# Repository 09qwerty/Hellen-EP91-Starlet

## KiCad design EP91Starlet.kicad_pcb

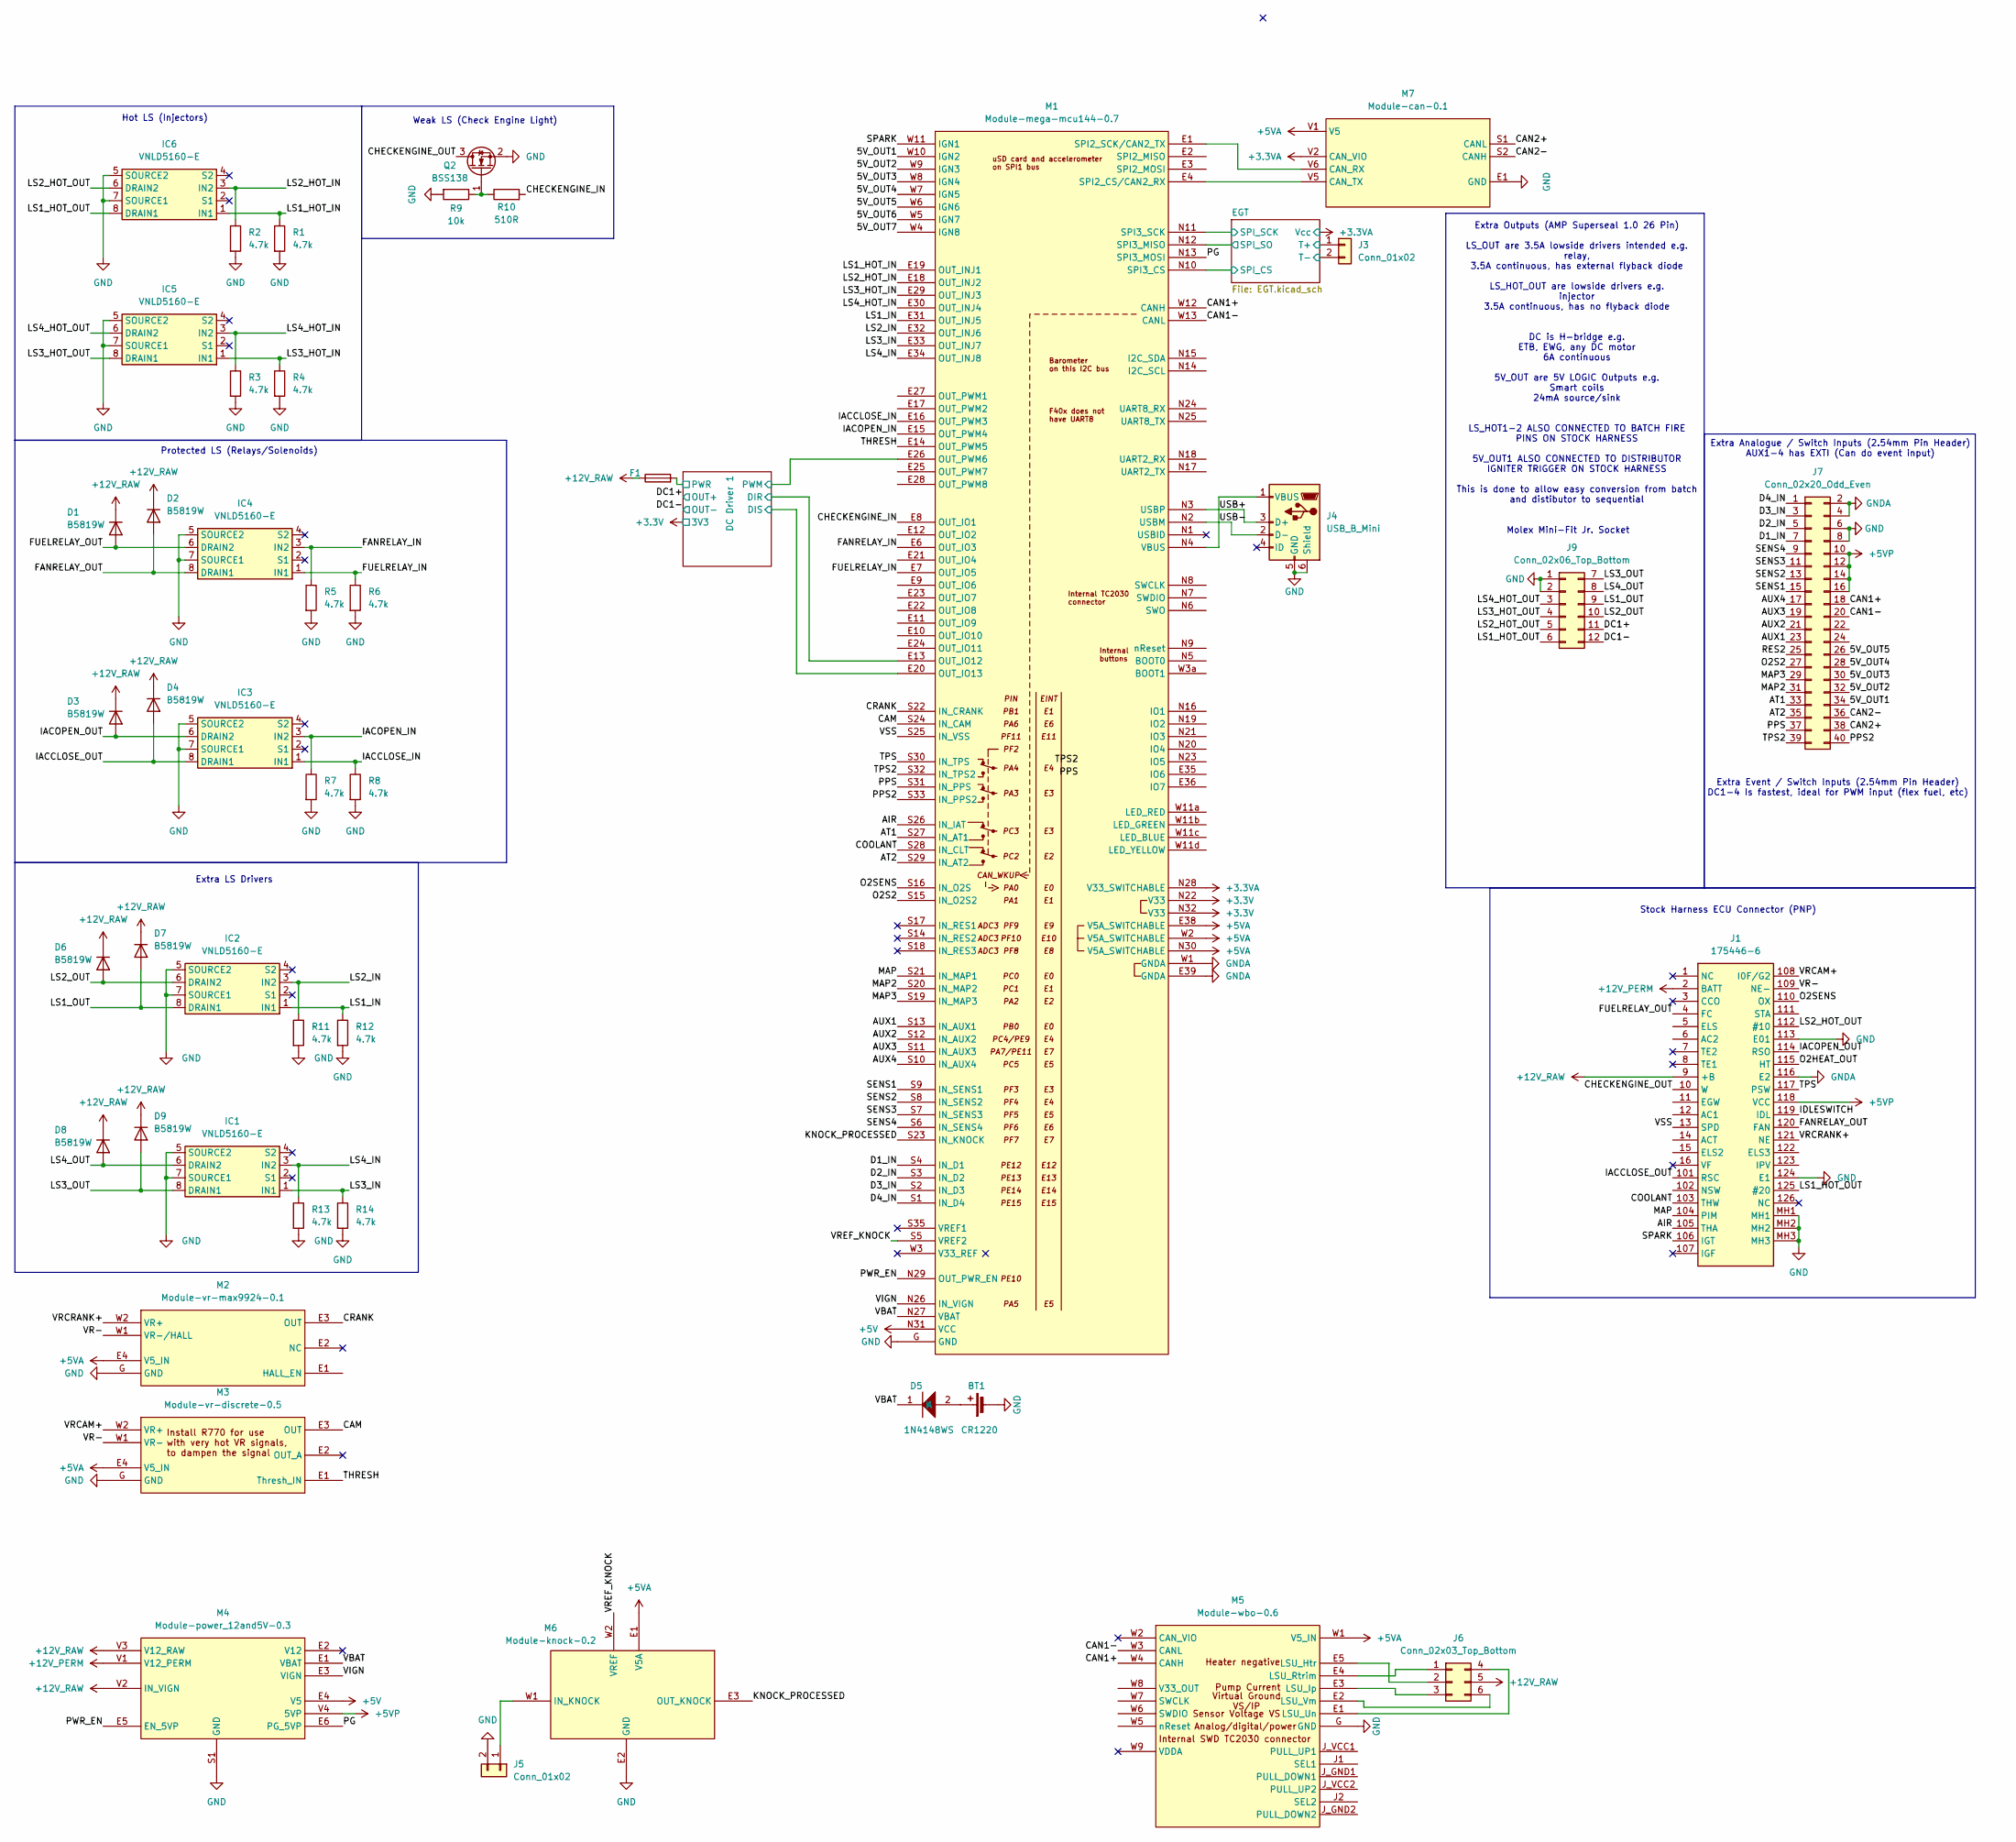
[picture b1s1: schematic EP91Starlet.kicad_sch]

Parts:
BT1: CR1220; CR1220-2; LCSC C70381
D1, D2, D3, D4, D6, D7, D8, D9: B5819W; D_SOD-123
D5: 1N4148WS; D_SOD-323; LCSC C2128
F1: Fuse; Fuse_1206_3216Metric_Pad1.42x1.75mm_HandSolder; LCSC C182446
IC1, IC2, IC3, IC4, IC5, IC6: VNLD5160-E; SOIC127P600X175-8N; Mouser Part Number 511-VNLD5160TR-E
J1: 175446-6; 1754466; Mouser Part Number 571-175446-6
J3, J5: Conn_01x02; PinHeader_1x02_P2.54mm_Vertical
J4: USB_B_Mini; USB_Mini-B_Wuerth_65100516121_Horizontal
J6: Conn_02x03_Top_Bottom; Molex_Mini-Fit_Jr_5566-06A_2x03_P4.20mm_Vertical
J7: Conn_02x20_Odd_Even; IDC-Header_2x20_P2.54mm_Vertical
J9: Conn_02x06_Top_Bottom; Molex_Mini-Fit_Jr_5566-12A_2x06_P4.20mm_Vertical
M1: Module-mega-mcu144-0.7; mega-mcu144
M2: Module-vr-max9924-0.1; vr-max9924
M3: Module-vr-discrete-0.5; vr-discrete
M4: Module-power_12and5V-0.3; power_12and5V
M5: Module-wbo-0.6; wbo
M6: Module-knock-0.2; knock
M7: Module-can-0.1; can
Q2: BSS138; SOT-23
R1, R2, R3, R4, R5, R6, R7, R8, R11, R12, R13, R14: 4.7k; R_0402_1005Metric
R9: 10k; R_0402_1005Metric
R10: 510R; R_0402_1005Metric

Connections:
+3.3V: M1.N22 (V33), M1.N32 (V33); also elsewhere on the board
+3.3VA: M1.N28 (V33_SWITCHABLE), M7.V2 (CAN_VIO); also elsewhere on the board
+5V: M1.N31 (VCC), M4.E4 (V5)
+5VA: M1.E38 (V5A_SWITCHABLE), M1.N30 (V5A_SWITCHABLE), M1.W2 (V5A_SWITCHABLE), M2.E4 (V5_IN), M3.E4 (V5_IN), M5.W1 (V5_IN), M6.E1 (V5A), M7.V1 (V5)
+5VP: J1.118 (VCC), J7.10, J7.12, J7.14, J7.16, M4.V4 (5VP)
+12V_PERM: J1.2 (BATT), M4.V1 (V12_PERM)
+12V_RAW: D1.1 (K), D2.1 (K), D3.1 (K), D4.1 (K), D6.1 (K), D7.1 (K), D8.1 (K), D9.1 (K), F1.1, J1.9 (+B), J6.5, M4.V2 (IN_VIGN), M4.V3 (V12_RAW)
/5V_OUT1: J7.34, M1.W10 (IGN2)
/5V_OUT2: J7.32, M1.W9 (IGN3)
/5V_OUT3: J7.30, M1.W8 (IGN4)
/5V_OUT4: J7.28, M1.W7 (IGN5)
/5V_OUT5: J7.26, M1.W6 (IGN6)
/5V_OUT6: M1.W5 (IGN7)
/5V_OUT7: M1.W4 (IGN8)
/AIR: J1.105 (THA), M1.S26 (IN_IAT)
/AT1: J7.33, M1.S27 (IN_AT1)
/AT2: J7.35, M1.S29 (IN_AT2)
/AUX1: J7.23, M1.S13 (IN_AUX1)
/AUX2: J7.21, M1.S12 (IN_AUX2)
/AUX3: J7.19, M1.S11 (IN_AUX3)
/AUX4: J7.17, M1.S10 (IN_AUX4)
/CAM: M1.S24 (IN_CAM), M3.E3 (OUT)
/CAN1+: J7.18, M1.W12 (CANH), M5.W4 (CANH)
/CAN1-: J7.20, M1.W13 (CANL), M5.W3 (CANL)
/CAN2+: J7.38, M7.S1 (CANL)
/CAN2-: J7.36, M7.S2 (CANH)
/CHECKENGINE_IN: M1.E8 (OUT_IO1), R10.2
/CHECKENGINE_OUT: J1.10 (W), Q2.3 (D)
/COOLANT: J1.103 (THW), M1.S28 (IN_CLT)
/CRANK: M1.S22 (IN_CRANK), M2.E3 (OUT)
/D1_IN: J7.7, M1.S4 (IN_D1)
/D2_IN: J7.5, M1.S3 (IN_D2)
/D3_IN: J7.3, M1.S2 (IN_D3)
/D4_IN: J7.1, M1.S1 (IN_D4)
/DC1+: J9.11; also elsewhere on the board
/DC1-: J9.12; also elsewhere on the board
/DC Driver 1/DIR: M1.E13 (OUT_IO12); also elsewhere on the board
/DC Driver 1/DIS: M1.E20 (OUT_IO13); also elsewhere on the board
/DC Driver 1/PWM: M1.E26 (OUT_PWM6); also elsewhere on the board
/DC Driver 1/PWR: F1.2; also elsewhere on the board
/EGT/SPI_CS: M1.N10 (SPI3_CS); also elsewhere on the board
/EGT/SPI_SCK: M1.N11 (SPI3_SCK); also elsewhere on the board
/EGT/SPI_SO: M1.N12 (SPI3_MISO); also elsewhere on the board
/EGT/T+: J3.1; also elsewhere on the board
/EGT/T-: J3.2; also elsewhere on the board
/FANRELAY_IN: IC4.3 (IN2), M1.E6 (OUT_IO3), R5.1
/FANRELAY_OUT: D2.2 (A), IC4.8 (DRAIN1), J1.120 (FAN)
/FUELRELAY_IN: IC4.1 (IN1), M1.E7 (OUT_IO5), R6.1
/FUELRELAY_OUT: D1.2 (A), IC4.6 (DRAIN2), J1.4 (FC)
/IACCLOSE_IN: IC3.1 (IN1), M1.E16 (OUT_PWM3), R8.1
/IACCLOSE_OUT: D4.2 (A), IC3.8 (DRAIN1), J1.101 (RSC)
/IACOPEN_IN: IC3.3 (IN2), M1.E15 (OUT_PWM4), R7.1
/IACOPEN_OUT: D3.2 (A), IC3.6 (DRAIN2), J1.114 (RSO)
/IDLESWITCH: J1.119 (IDL)
/KNOCK_PROCESSED: M1.S23 (IN_KNOCK), M6.E3 (OUT_KNOCK)
/LS1_HOT_IN: IC6.1 (IN1), M1.E19 (OUT_INJ1), R1.1
/LS1_HOT_OUT: IC6.8 (DRAIN1), J1.125 (#20), J9.6
/LS1_IN: IC2.1 (IN1), M1.E31 (OUT_INJ5), R12.1
/LS1_OUT: D7.2 (A), IC2.8 (DRAIN1), J9.9
/LS2_HOT_IN: IC6.3 (IN2), M1.E18 (OUT_INJ2), R2.1
/LS2_HOT_OUT: IC6.6 (DRAIN2), J1.112 (#10), J9.5
/LS2_IN: IC2.3 (IN2), M1.E32 (OUT_INJ6), R11.1
/LS2_OUT: D6.2 (A), IC2.6 (DRAIN2), J9.10
/LS3_HOT_IN: IC5.1 (IN1), M1.E29 (OUT_INJ3), R4.1
/LS3_HOT_OUT: IC5.8 (DRAIN1), J9.4
/LS3_IN: IC1.1 (IN1), M1.E33 (OUT_INJ7), R14.1
/LS3_OUT: D9.2 (A), IC1.8 (DRAIN1), J9.7
/LS4_HOT_IN: IC5.3 (IN2), M1.E30 (OUT_INJ4), R3.1
/LS4_HOT_OUT: IC5.6 (DRAIN2), J9.3
/LS4_IN: IC1.3 (IN2), M1.E34 (OUT_INJ8), R13.1
/LS4_OUT: D8.2 (A), IC1.6 (DRAIN2), J9.8
/MAP: J1.104 (PIM), M1.S21 (IN_MAP1)
/MAP2: J7.31, M1.S20 (IN_MAP2)
/MAP3: J7.29, M1.S19 (IN_MAP3)
/O2HEAT_OUT: J1.115 (HT)
/O2S2: J7.27, M1.S15 (IN_O2S2)
/O2SENS: J1.110 (OX), M1.S16 (IN_O2S)
/PG: M1.N13 (SPI3_MOSI), M4.E6 (PG_5VP)
/PPS: J7.37, M1.S31 (IN_PPS)
/PPS2: J7.40, M1.S33 (IN_PPS2)
/PWR_EN: M1.N29 (OUT_PWR_EN), M4.E5 (EN_5VP)
/RES2: J7.25
/SENS1: J7.15, M1.S9 (IN_SENS1)
/SENS2: J7.13, M1.S8 (IN_SENS2)
/SENS3: J7.11, M1.S7 (IN_SENS3)
/SENS4: J7.9, M1.S6 (IN_SENS4)
/SPARK: J1.106 (IGT), M1.W11 (IGN1)
/THRESH: M1.E14 (OUT_PWM5), M3.E1 (Thresh_IN)
/TPS: J1.117 (PSW), M1.S30 (IN_TPS)
/TPS2: J7.39, M1.S32 (IN_TPS2)
/VBAT: D5.1 (K), M1.N27 (VBAT), M4.E1 (VBAT)
/VIGN: M1.N26 (IN_VIGN), M4.E3 (VIGN)
/VR-: J1.109 (NE-), M2.W1 (VR-/HALL), M3.W1 (VR-)
/VRCAM+: J1.108 (I0F/G2), M3.W2 (VR+)
/VRCRANK+: J1.121 (NE), M2.W2 (VR+)
/VREF_KNOCK: M1.S5 (VREF2), M6.W2 (VREF)
/VSS: J1.13 (SPD), M1.S25 (IN_VSS)
GND: BT1.2 (-), IC1.5 (SOURCE2), IC1.7 (SOURCE1), IC2.5 (SOURCE2), IC2.7 (SOURCE1), IC3.5 (SOURCE2), IC3.7 (SOURCE1), IC4.5 (SOURCE2), IC4.7 (SOURCE1), IC5.5 (SOURCE2), IC5.7 (SOURCE1), IC6.5 (SOURCE2), IC6.7 (SOURCE1), J1.113 (E01), J1.124 (E1), J1.MH1, J1.MH2, J1.MH3, J4.5 (GND), J4.6 (Shield), J5.2, J7.6, J7.8, J9.1, J9.2, M1.G (GND), M2.G (GND), M3.G (GND), M4.S1 (GND), M5.G (GND), M6.E2 (GND), M7.E1 (GND), Q2.2 (S), R1.2, R2.2, R3.2, R4.2, R5.2, R6.2, R7.2, R8.2, R9.2, R11.2, R12.2, R13.2, R14.2; also elsewhere on the board
GNDA: J1.116 (E2), J7.2, J7.4, M1.E39 (GNDA), M1.W1 (GNDA)
unnamed: BT1.1 (+), D5.2 (A)
unnamed: J5.1, M6.W1 (IN_KNOCK)
unnamed: J6.1, M5.E4 (LSU_Rtrim)
unnamed: J6.2, M5.E5 (LSU_Htr)
unnamed: J6.3, M5.E3 (LSU_Ip)
unnamed: J6.4, M5.E1 (LSU_Un)
unnamed: J6.6, M5.E2 (LSU_Vm)
unnamed: M1.E4 (SPI2_CS/CAN2_RX), M7.V5 (CAN_TX)
unnamed: M1.E1 (SPI2_SCK/CAN2_TX), M7.V6 (CAN_RX)
unnamed: Q2.1 (G), R9.1, R10.1

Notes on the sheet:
Stock Harness ECU Connector (PNP)
Extra Outputs (AMP Superseal 1.0 26 Pin) LS_OUT are 3.5A lowside drivers intended e.g. relay, 3.5A continuous, has external flyback diode LS_HOT_OUT are lowside drivers e.g. injector 3.5A continuous, has no flyback diode DC is H-bridge e.g. ETB, EWG, any DC motor 6A continuous 5V_OUT are 5V LOGIC O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
Extra Event / Switch Inputs (2.54mm Pin Header) DC1-4 Is fastest, ideal for PWM input (flex fuel, etc)
Hot LS (Injectors)
Extra LS Drivers
Molex Mini-Fit Jr. Socket
Weak LS (Check Engine Light)
Extra Analogue / Switch Inputs (2.54mm Pin Header) AUX1-4 has EXTI (Can do event input)
Protected LS (Relays/Solenoids)

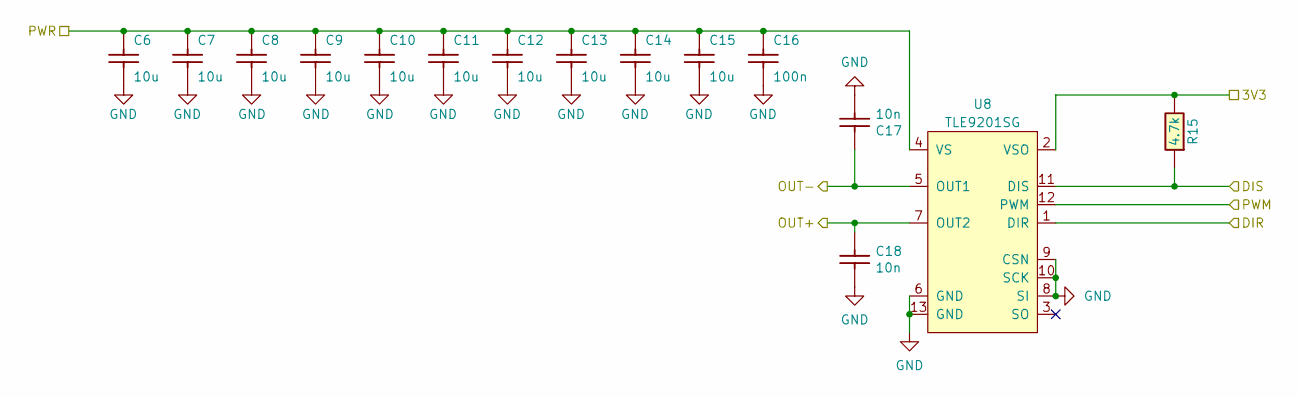
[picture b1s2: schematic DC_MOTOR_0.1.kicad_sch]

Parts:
C6, C7, C8, C9, C10, C11, C12, C13, C14, C15: 10u; C_0603_1608Metric; LCSC C15850
C16: 100n; C_0603_1608Metric; LCSC C14663
C17, C18: 10n; C_0603_1608Metric; LCSC C57112
R15: 4.7k; R_0603_1608Metric; LCSC C23162
U8: TLE9201SG; Infineon_PG-DSO-12-11; LCSC C112633

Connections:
+3.3V: R15.2, U8.2 (VSO); also elsewhere on the board
/DC1+: C18.2, U8.7 (OUT2); also elsewhere on the board
/DC1-: C17.2, U8.5 (OUT1); also elsewhere on the board
/DC Driver 1/DIR: U8.1 (DIR); also elsewhere on the board
/DC Driver 1/DIS: R15.1, U8.11 (DIS); also elsewhere on the board
/DC Driver 1/PWM: U8.12 (PWM); also elsewhere on the board
/DC Driver 1/PWR: C6.2, C7.2, C8.2, C9.2, C10.2, C11.2, C12.2, C13.2, C14.2, C15.2, C16.2, U8.4 (VS); also elsewhere on the board
GND: C6.1, C7.1, C8.1, C9.1, C10.1, C11.1, C12.1, C13.1, C14.1, C15.1, C16.1, C17.1, C18.1, U8.6 (GND), U8.8 (SI), U8.9 (CSN), U8.10 (SCK), U8.13 (GND); also elsewhere on the board

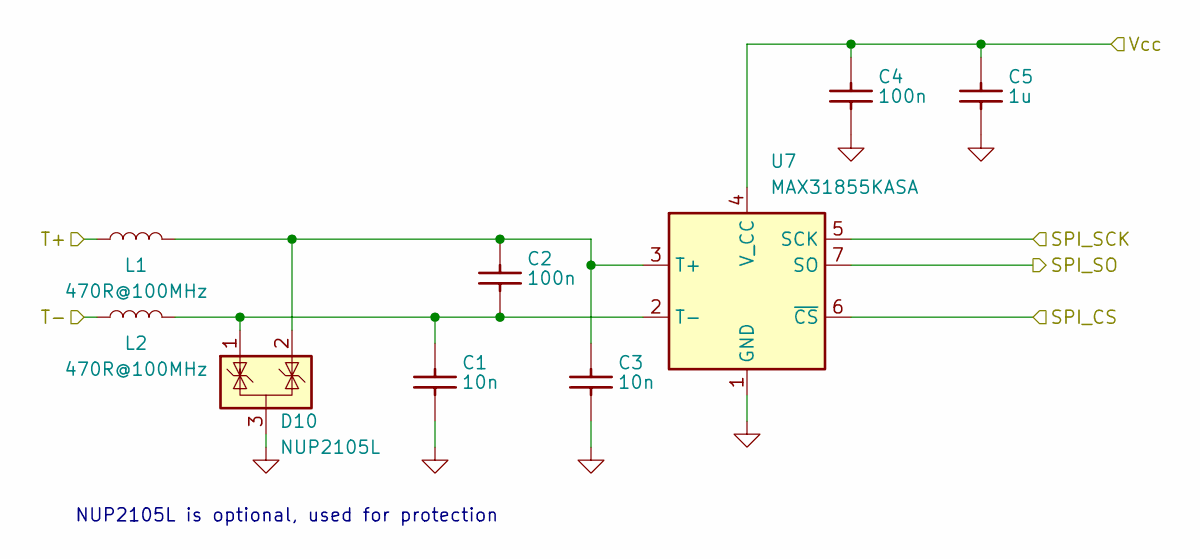
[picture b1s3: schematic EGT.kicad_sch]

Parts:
C1, C3: 10n; C_0603_1608Metric; LCSC C57112
C2, C4: 100n; C_0603_1608Metric; LCSC C14663
C5: 1u; C_0603_1608Metric; LCSC C15849
D10: NUP2105L; SOT-23; LCSC C284104
L1, L2: 470R@100MHz; L_0603_1608Metric; LCSC C97853
U7: MAX31855KASA; SOIC-8_3.9x4.9mm_P1.27mm; LCSC C52028

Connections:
+3.3VA: C4.2, C5.2, U7.4 (V_CC); also elsewhere on the board
/EGT/SPI_CS: U7.6 (~CS); also elsewhere on the board
/EGT/SPI_SCK: U7.5 (SCK); also elsewhere on the board
/EGT/SPI_SO: U7.7 (SO); also elsewhere on the board
/EGT/T+: L1.1; also elsewhere on the board
/EGT/T-: L2.1; also elsewhere on the board
GND: C1.1, C3.1, C4.1, C5.1, D10.3 (A), U7.1 (GND); also elsewhere on the board
unnamed: C2.2, C3.2, D10.2 (K), L1.2, U7.3 (T+)
unnamed: C1.2, C2.1, D10.1 (K), L2.2, U7.2 (T-)

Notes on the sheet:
NUP2105L is optional, used for protection

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
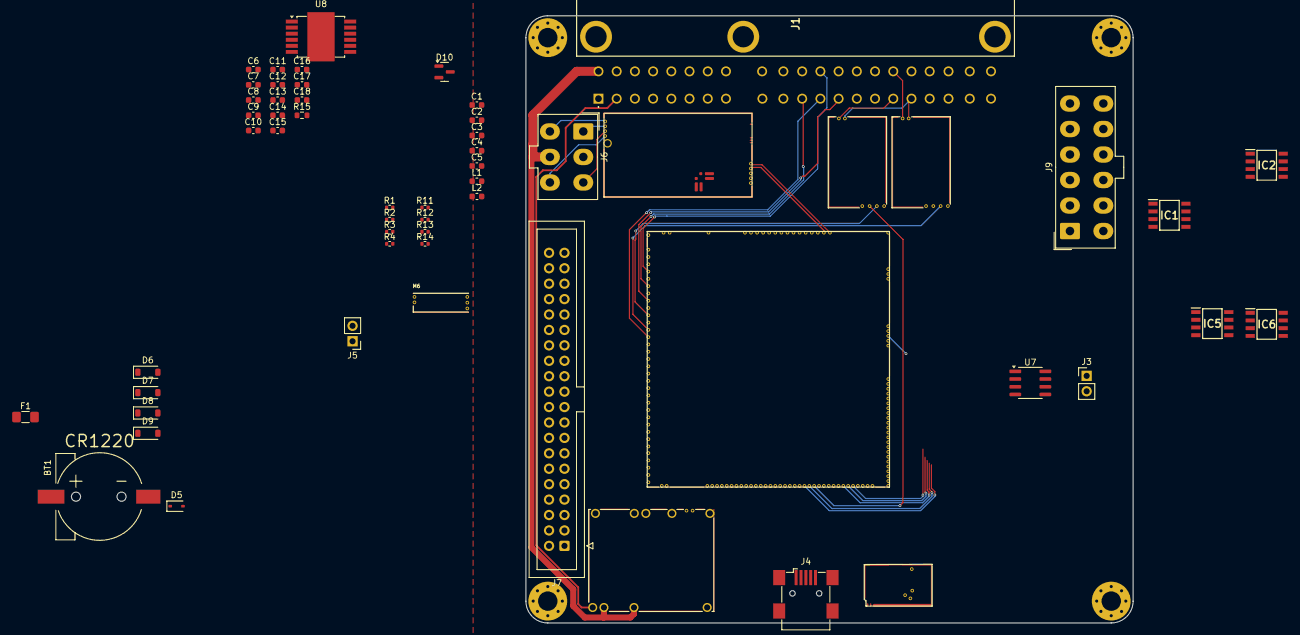
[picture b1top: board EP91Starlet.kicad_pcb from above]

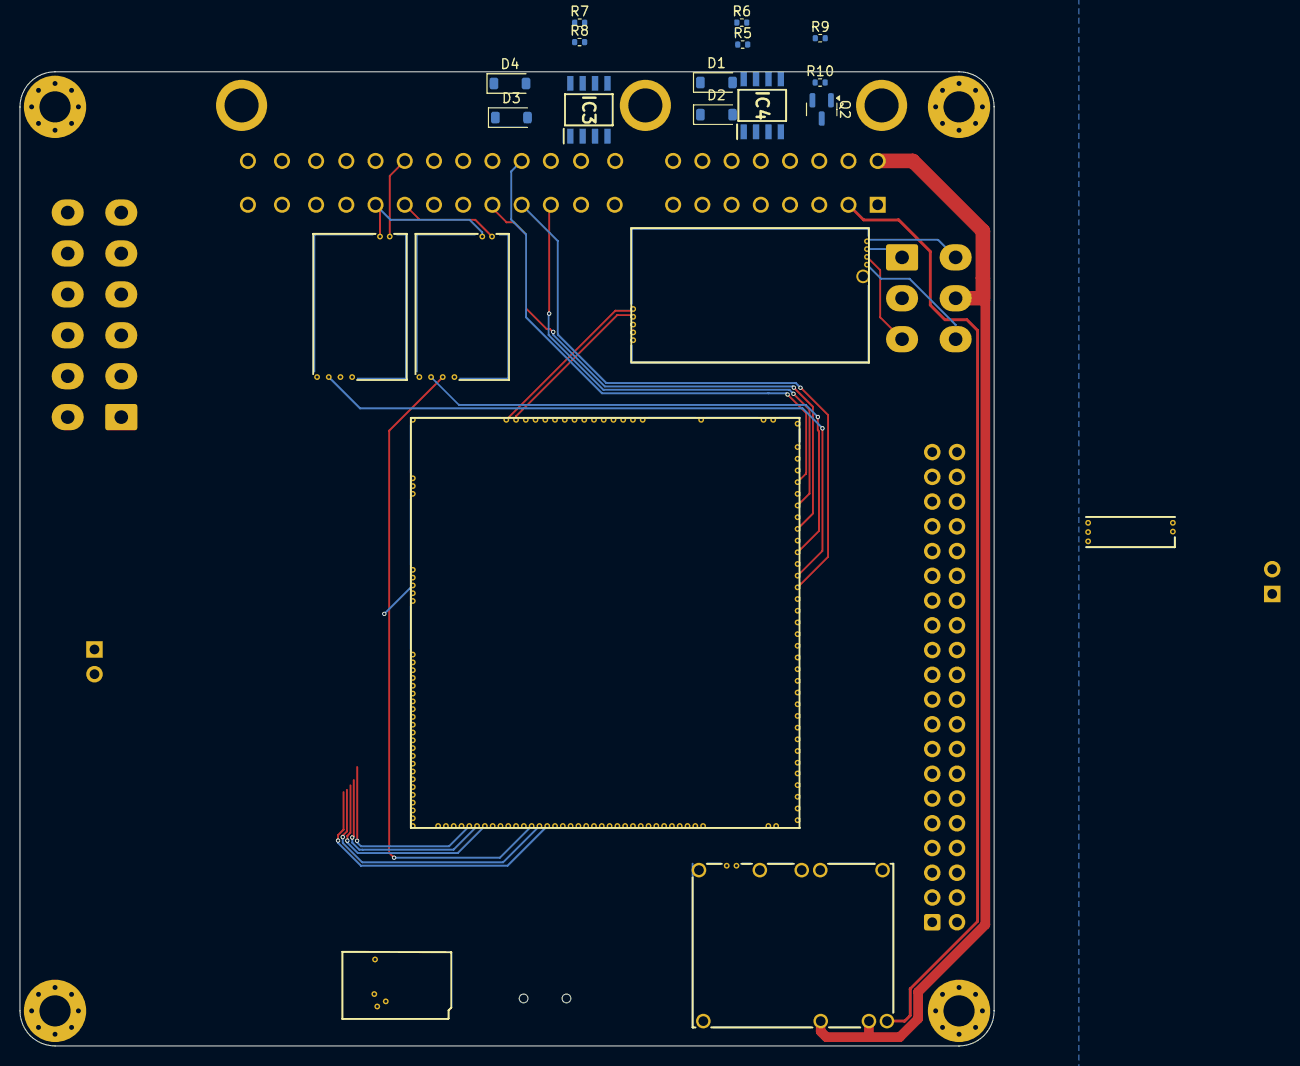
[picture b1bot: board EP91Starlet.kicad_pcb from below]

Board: 4 copper layers, 100.0 x 100.0 mm, 70 parts (13 on the bottom side), 109 nets.

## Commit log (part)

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2025-05-16 Inital project files
2025-05-16 Importing modules
2025-05-16 Corrected aux axis position
2025-05-16 [skip actions] Auto-generated board v2.1
2025-05-16 Fixed bom
2025-05-16 made ecu connector footprint
2025-05-16 more testing
2025-05-16 Test2
2025-05-16 fix bom
2025-05-16 Fix pcb layers
2025-05-19 65urft7ih
2025-06-13 Pin mapping
2025-06-13 update pin maps
2025-06-16 add submodules for ign and inj + flyback protected output
2025-06-20 GHA says update hellen-one
2025-09-23 put in local files
2026-02-05 retry (last time i promise :))
2026-02-05 GHA says update kicad6-libraries
2026-03-14 sync
